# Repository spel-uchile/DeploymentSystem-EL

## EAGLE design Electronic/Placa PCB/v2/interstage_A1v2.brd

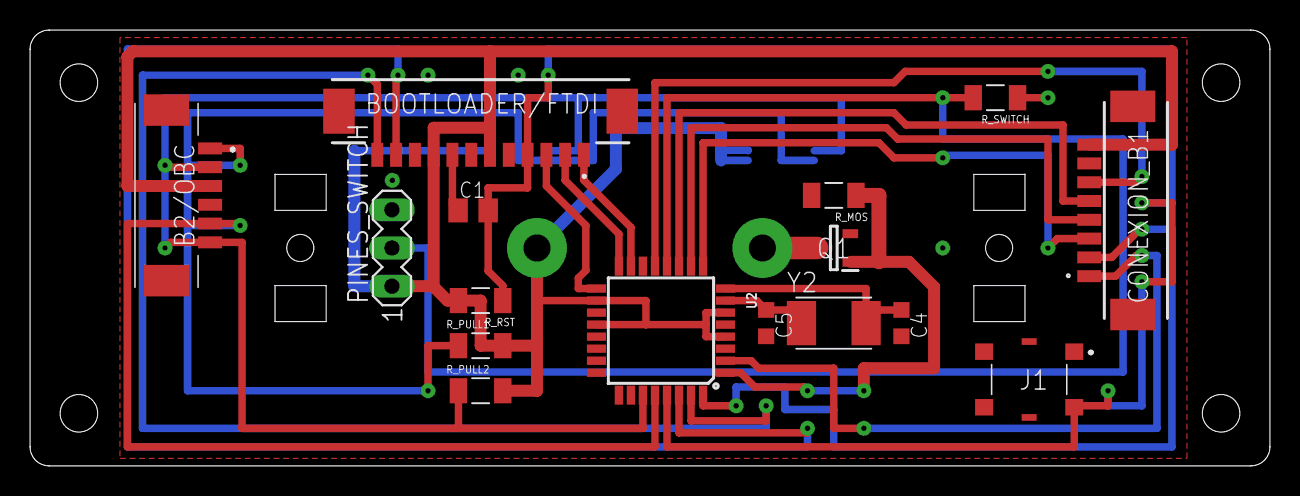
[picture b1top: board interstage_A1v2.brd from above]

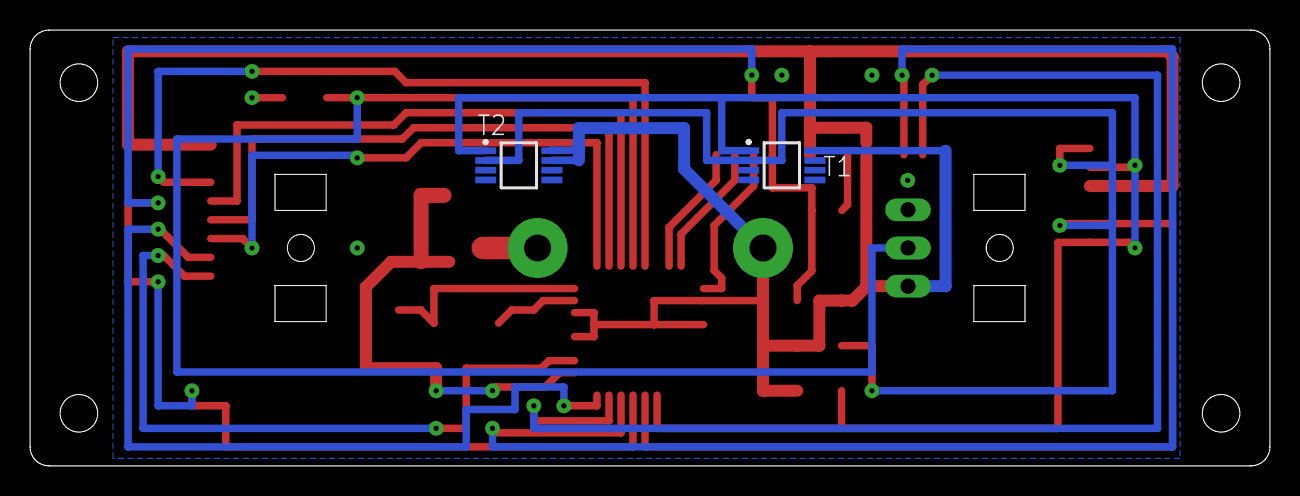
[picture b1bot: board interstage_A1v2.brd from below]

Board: 2 copper layers, 82.5 x 29.0 mm, 18 parts (2 on the bottom side), 21 nets.

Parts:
B2/OBC: 53261-7006; 532617006
BOOTLOADER/FTDI: 53261-1271
C1: 100nF; C0805K
C4, C5: 22pF; C0603K
CONEXION_B1: 53261-0871
J1: 431151015826
PINES_SWITCH: MA03-1
Q1: PMV16XNR; SOT95P230X110-3N
R_MOS: ERA-8AEB331V; RESC3216X70N
R_PULL1, R_PULL2: ERA-8AEB472V; RESC3216X70N
R_RST: ERA-8AEB103V; RESC3216X70N
R_SWITCH: ERA-8AEB331V; RESC3216X70N
T1, T2: MCP9808T-E/MS; SOP65P490X110-8N
U2: ATMEGA328P_TQFP; TQFP32-08
Y2: ABM3-16.000MHZ-D2Y-T; XTAL500X320X130N

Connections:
AIN0: CONEXION_B1.4, U2.10
AIN1: CONEXION_B1.5, U2.11
DTR: BOOTLOADER/FTDI.8, C1.1
GND: B2/OBC.4, BOOTLOADER/FTDI.5, BOOTLOADER/FTDI.10, C4.2, C5.2, CONEXION_B1.7, J1.3, J1.5, J1.6, Q1.2, R_MOS.2, R_SWITCH.1, T1.4, T1.5, T1.6, T1.7, T2.4, T2.5, T2.6, U2.3, U2.5
INT0: CONEXION_B1.2, U2.32
INT1: Q1.1, R_MOS.1, U2.1
MISO: BOOTLOADER/FTDI.2, U2.16
MOSI: BOOTLOADER/FTDI.1, U2.15
unnamed: C5.1, U2.7, Y2.1
unnamed: C4.1, U2.8, Y2.2
OC1A: CONEXION_B1.6, U2.13
RST: BOOTLOADER/FTDI.4, C1.2, J1.2, R_RST.1, U2.29
RXD: BOOTLOADER/FTDI.11, U2.30
SCK: BOOTLOADER/FTDI.3, U2.17
SCL: B2/OBC.1, B2/OBC.5, R_PULL1.1, T1.2, T2.2, U2.28
SDA: B2/OBC.2, B2/OBC.6, R_PULL2.1, T1.1, T2.1, U2.27
SWITCH: PINES_SWITCH.2, R_SWITCH.2, U2.12
T0: CONEXION_B1.1, U2.2
T1: CONEXION_B1.3, U2.9
TXD: BOOTLOADER/FTDI.12, U2.31
VCC: B2/OBC.3, BOOTLOADER/FTDI.6, BOOTLOADER/FTDI.9, CONEXION_B1.8, PINES_SWITCH.1, R_PULL1.2, R_PULL2.2, R_RST.2, T1.8, T2.7, T2.8, U2.4, U2.6, U2.18, U2.20

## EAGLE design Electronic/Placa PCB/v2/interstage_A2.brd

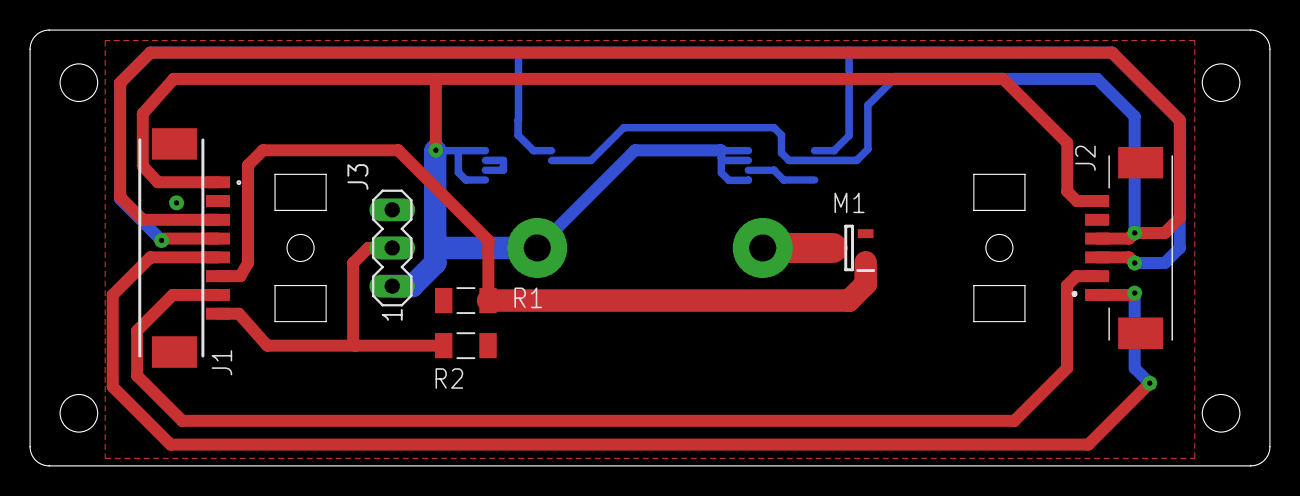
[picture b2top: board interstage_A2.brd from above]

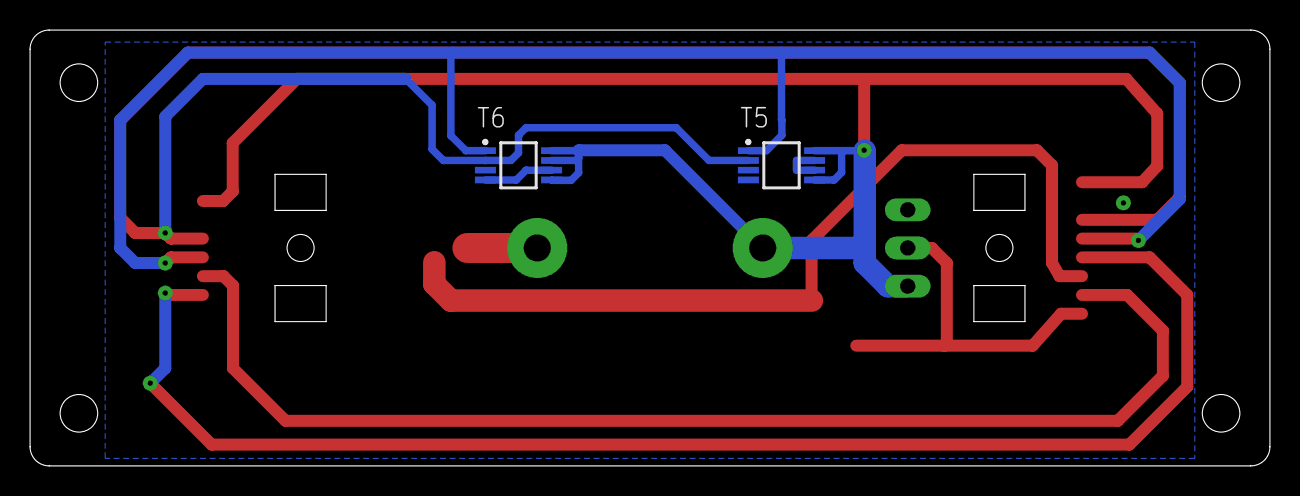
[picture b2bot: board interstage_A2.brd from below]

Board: 2 copper layers, 82.5 x 29.0 mm, 8 parts (2 on the bottom side), 8 nets.

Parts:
J1: 53261-0871
J2: 53261-7006; 532617006
J3: MA03-1
M1: PMV16XNR; SOT95P230X110-3N
R1, R2: 330; RESC3216X70N
T5, T6: MCP9808T-E/MS; SOP65P490X110-8N

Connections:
AIN0: J1.6, M1.1, R1.1
GND: J1.2, J2.5, M1.2, R1.2, R2.1, T5.4, T5.6, T5.7, T6.4, T6.6
INT0: J1.7, J2.2
OC1A: J1.5, J2.1
SCL: J1.3, J2.4, T5.2, T6.2
SDA: J1.4, J2.3, T5.1, T6.1
T0: J1.8, J3.2, R2.2
VCC: J1.1, J2.6, J3.1, T5.5, T5.8, T6.5, T6.7, T6.8

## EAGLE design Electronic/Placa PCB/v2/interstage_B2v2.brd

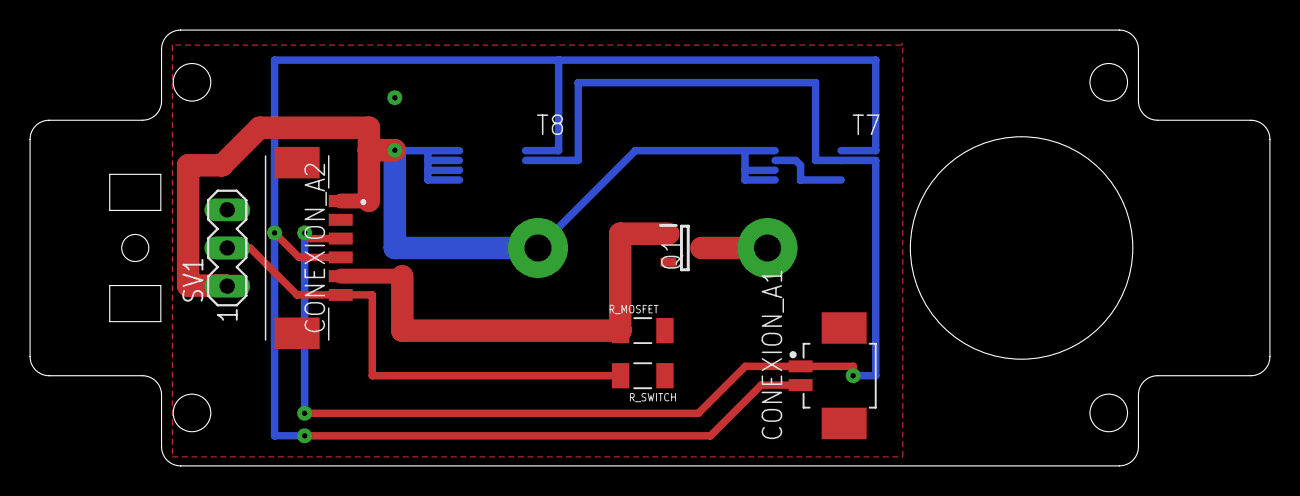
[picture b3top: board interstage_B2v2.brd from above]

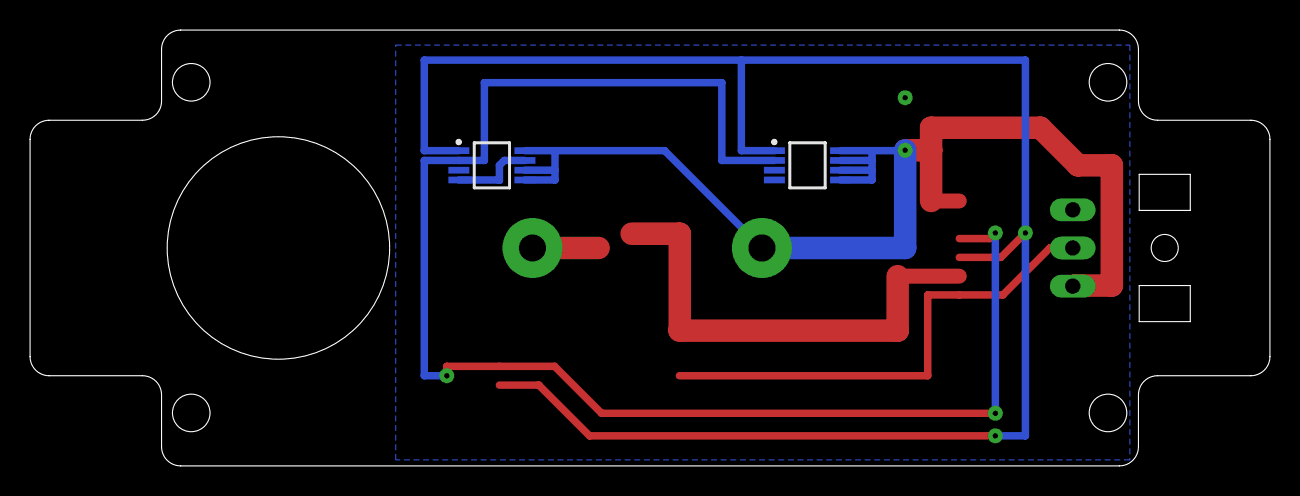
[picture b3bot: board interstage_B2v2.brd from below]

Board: 2 copper layers, 82.5 x 29.0 mm, 8 parts (2 on the bottom side), 6 nets.

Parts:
CONEXION_A1: 0532610271; MOLEX_0532610271
CONEXION_A2: 53261-7006; 532617006
Q1: PMV16XNR; SOT95P230X110-3N
R_MOSFET: ERA-8AEB331V; RESC3216X70N
R_SWITCH: ERA-8AEB331V; RESC3216X70N
SV1: MA03-1
T7, T8: MCP9808T-E/MS; SOP65P490X110-8N

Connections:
GND: CONEXION_A2.2, Q1.2, R_MOSFET.2, R_SWITCH.1, T7.4, T7.7, T8.4
INT0: CONEXION_A2.6, R_SWITCH.2, SV1.2
OC1A: CONEXION_A2.5, Q1.1, R_MOSFET.1
SCL: CONEXION_A1.1, CONEXION_A2.3, T7.2, T8.2
SDA: CONEXION_A1.2, CONEXION_A2.4, T7.1, T8.1
VCC: CONEXION_A2.1, SV1.1, T7.5, T7.6, T7.8, T8.5, T8.6, T8.7, T8.8

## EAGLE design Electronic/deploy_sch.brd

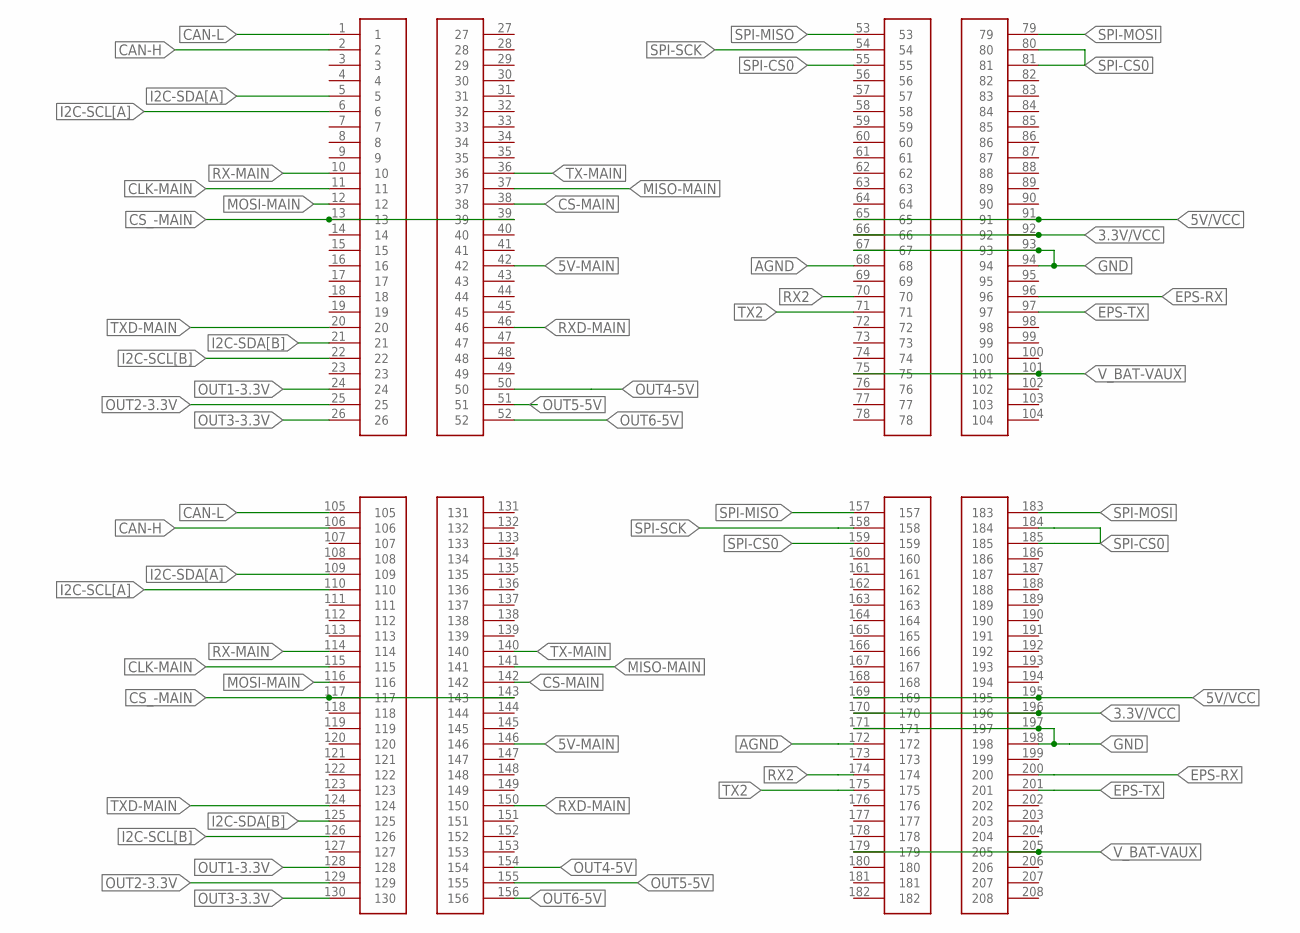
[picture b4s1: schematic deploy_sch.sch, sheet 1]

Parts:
U$1: SUCHAI_STACKBREAKOUT

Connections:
3.3V/VCC: U$1.66, U$1.92, U$1.170, U$1.196
5V-MAIN: U$1.42, U$1.146
5V/VCC: U$1.65, U$1.91, U$1.169, U$1.195
AGND: U$1.68, U$1.172
CAN-H: U$1.2, U$1.106
CAN-L: U$1.1, U$1.105
CLK-MAIN: U$1.11, U$1.115
CS-MAIN: U$1.38, U$1.142
CS_-MAIN: U$1.13, U$1.39, U$1.117, U$1.143
EPS-RX: U$1.96, U$1.200
EPS-TX: U$1.97, U$1.201
GND: U$1.67, U$1.93, U$1.94, U$1.171, U$1.197, U$1.198; also elsewhere on the board
I2C-SCL[A]: U$1.6, U$1.110
I2C-SCL[B]: U$1.22, U$1.126
I2C-SDA[A]: U$1.5, U$1.109
I2C-SDA[B]: U$1.21, U$1.125
MISO-MAIN: U$1.37, U$1.141
MOSI-MAIN: U$1.12, U$1.116
OUT1-3.3V: U$1.24, U$1.128
OUT2-3.3V: U$1.25, U$1.129; also elsewhere on the board
OUT3-3.3V: U$1.26, U$1.130
OUT4-5V: U$1.50, U$1.154
OUT5-5V: U$1.51, U$1.155; also elsewhere on the board
OUT6-5V: U$1.52, U$1.156
RX2: U$1.70, U$1.174
RX-MAIN: U$1.10, U$1.114
RXD-MAIN: U$1.46, U$1.150
SPI-CS0: U$1.55, U$1.80, U$1.81, U$1.159, U$1.184, U$1.185
SPI-MISO: U$1.53, U$1.157
SPI-MOSI: U$1.79, U$1.183
SPI-SCK: U$1.54, U$1.158
TX2: U$1.71, U$1.175
TX-MAIN: U$1.36, U$1.140
TXD-MAIN: U$1.20, U$1.124
V_BAT-VAUX: U$1.75, U$1.101, U$1.179, U$1.205

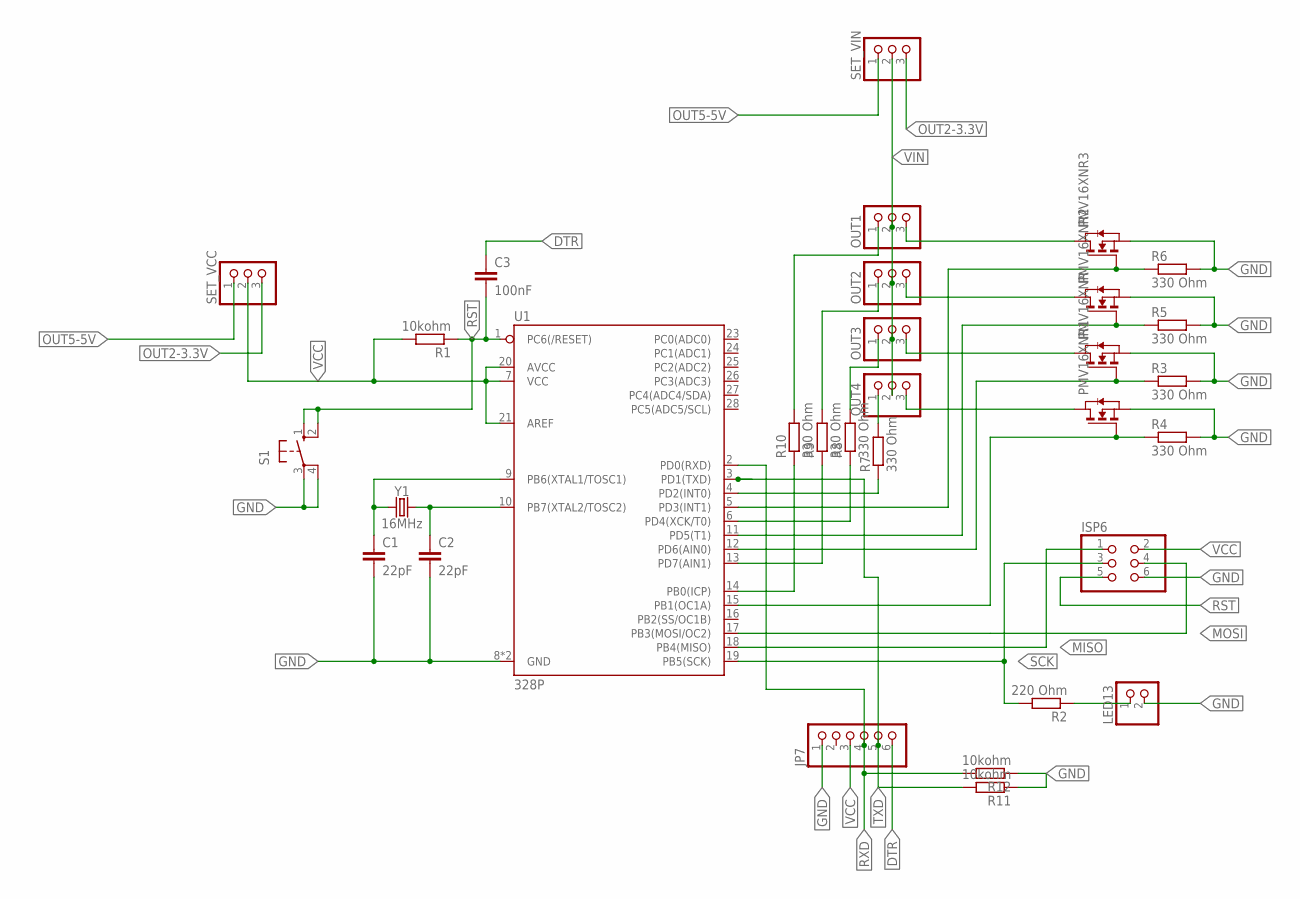
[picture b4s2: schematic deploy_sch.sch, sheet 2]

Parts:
C1, C2: 22pF; C025-025X050
C3: 100nF; C025-025X050
ISP6: PINHD-2X3; 2X03
JP7: PINHD-1X6; 1X06
LED13: PINHD-1X2; 1X02
OUT1, OUT2, OUT3, OUT4: PINHD-1X3; 1X03
PMV16XNR, PMV16XNR1, PMV16XNR2, PMV16XNR3: NMOSSOT23; SOT-23
R1, R11, R12: 10kohm; 0204/7
R2: 220 Ohm; 0204/7
R3, R4, R5, R6, R7, R8, R9, R10: 330 Ohm; 0204/7
S1: 10-XX; B3F-10XX
SET_VCC: PINHD-1X3; 1X03
SET_VIN: PINHD-1X3; 1X03
U1: 328P; DIP28
Y1: 16MHz; HC49US

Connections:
DTR: C3.1, JP7.6
GND: C1.2, C2.2, ISP6.6, JP7.1, LED13.2, PMV16XNR.2 (S), PMV16XNR1.2 (S), PMV16XNR2.2 (S), PMV16XNR3.2 (S), R3.2, R4.2, R5.2, R6.2, R11.1, R12.1, S1.3, S1.4 (P1), U1.8 (GND), U1.22 (GND); also elsewhere on the board
MISO: ISP6.1, U1.18 (PB4(MISO))
MOSI: ISP6.4, U1.17 (PB3(MOSI/OC2))
unnamed: C1.1, U1.9 (PB6(XTAL1/TOSC1)), Y1.1
unnamed: C2.1, U1.10 (PB7(XTAL2/TOSC2)), Y1.2
unnamed: PMV16XNR.3 (G), R3.1, U1.12 (PD6(AIN0))
unnamed: LED13.1, R2.1
unnamed: PMV16XNR1.3 (G), R4.1, U1.15 (PB1(OC1A))
unnamed: PMV16XNR2.3 (G), R5.1, U1.11 (PD5(T1))
unnamed: PMV16XNR3.3 (G), R6.1, U1.5 (PD3(INT1))
unnamed: OUT4.3, PMV16XNR1.1 (D)
unnamed: OUT3.3, PMV16XNR.1 (D)
unnamed: OUT2.3, PMV16XNR2.1 (D)
unnamed: OUT1.3, PMV16XNR3.1 (D)
unnamed: OUT4.1, R7.2
unnamed: R7.1, U1.4 (PD2(INT0))
unnamed: OUT3.1, R8.2
unnamed: R8.1, U1.6 (PD4(XCK/T0))
unnamed: R9.1, U1.13 (PD7(AIN1))
unnamed: OUT2.1, R9.2
unnamed: OUT1.1, R10.2
unnamed: R10.1, U1.14 (PB0(ICP))
OUT2-3.3V: SET_VCC.3, SET_VIN.3; also elsewhere on the board
OUT5-5V: SET_VCC.1, SET_VIN.1; also elsewhere on the board
RST: C3.2, ISP6.5, R1.1, S1.1 (S), S1.2 (S1), U1.1 (PC6(/RESET))
RXD: JP7.4, R12.2, U1.2 (PD0(RXD))
SCK: ISP6.3, R2.2, U1.19 (PB5(SCK))
TXD: JP7.5, R11.2, U1.3 (PD1(TXD))
VCC: ISP6.2, JP7.3, R1.2, SET_VCC.2, U1.7 (VCC), U1.20 (AVCC), U1.21 (AREF)
VIN: OUT1.2, OUT2.2, OUT3.2, OUT4.2, SET_VIN.2

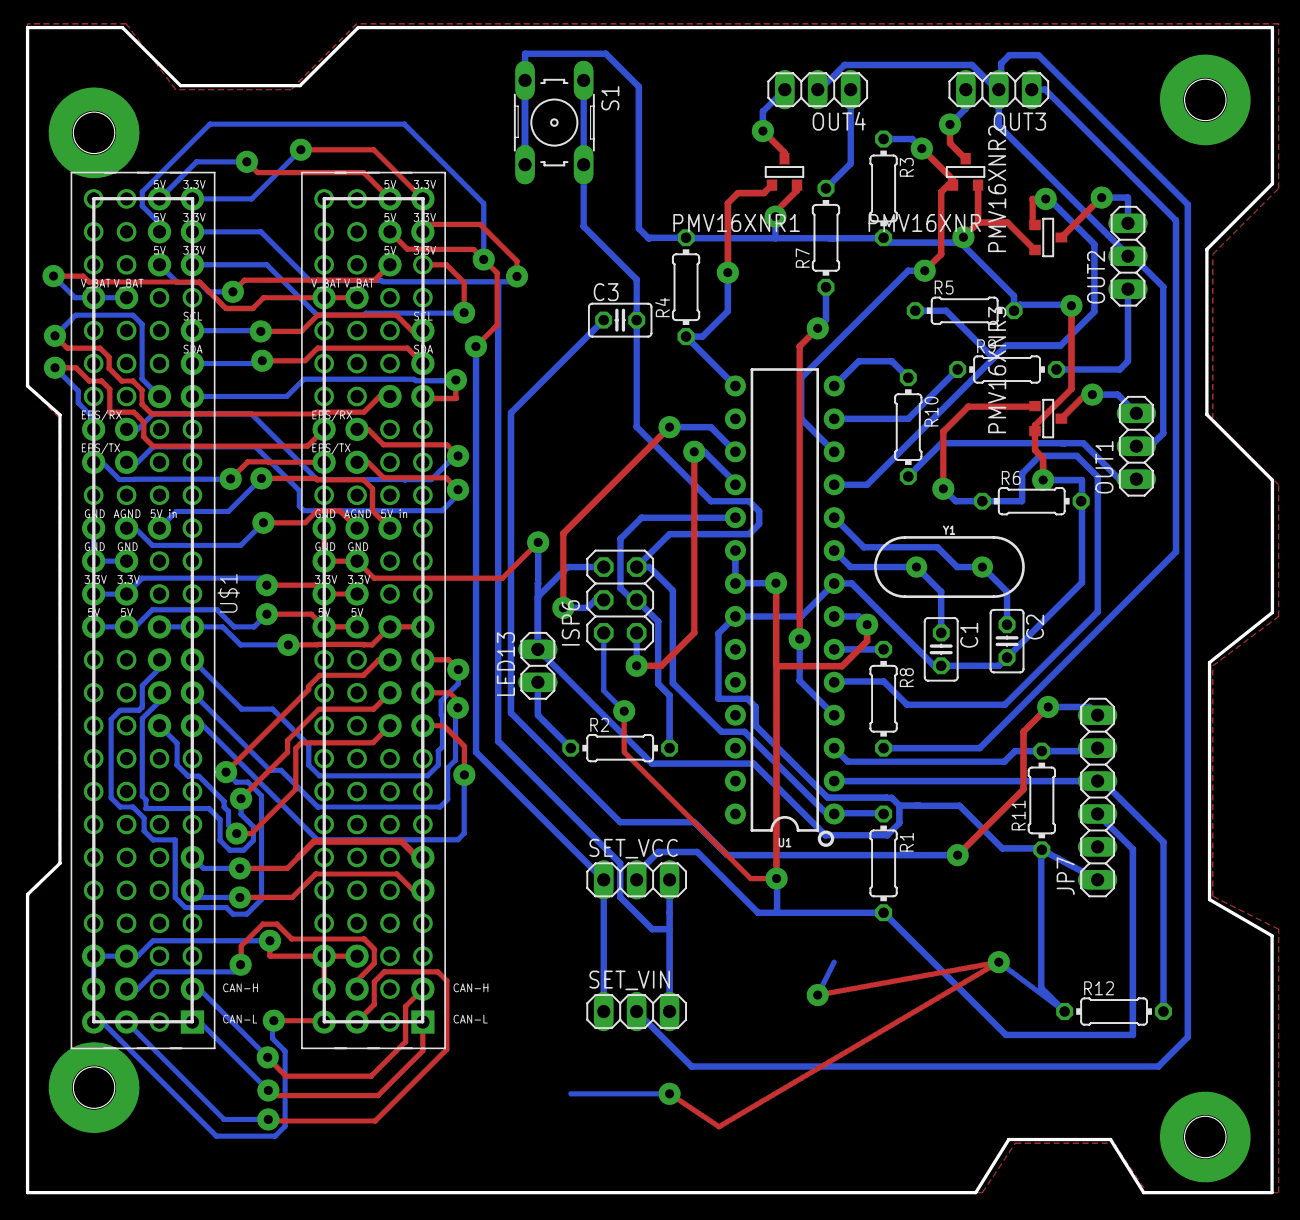
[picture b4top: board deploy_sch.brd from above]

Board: 2 copper layers, 96.2 x 90.0 mm, 32 parts (0 on the bottom side), 63 nets.

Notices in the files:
parts and their libraries:
SUCHAI_PCB: Licensing: Creative Commons ShareAlike 4.0 International - https://creativecommons.org/licenses/by-sa/4.0
